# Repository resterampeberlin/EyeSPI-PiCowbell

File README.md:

# Purpose

# Credits

This open source code project is has been proudfully produced in Berlin (and other places around the globe) by

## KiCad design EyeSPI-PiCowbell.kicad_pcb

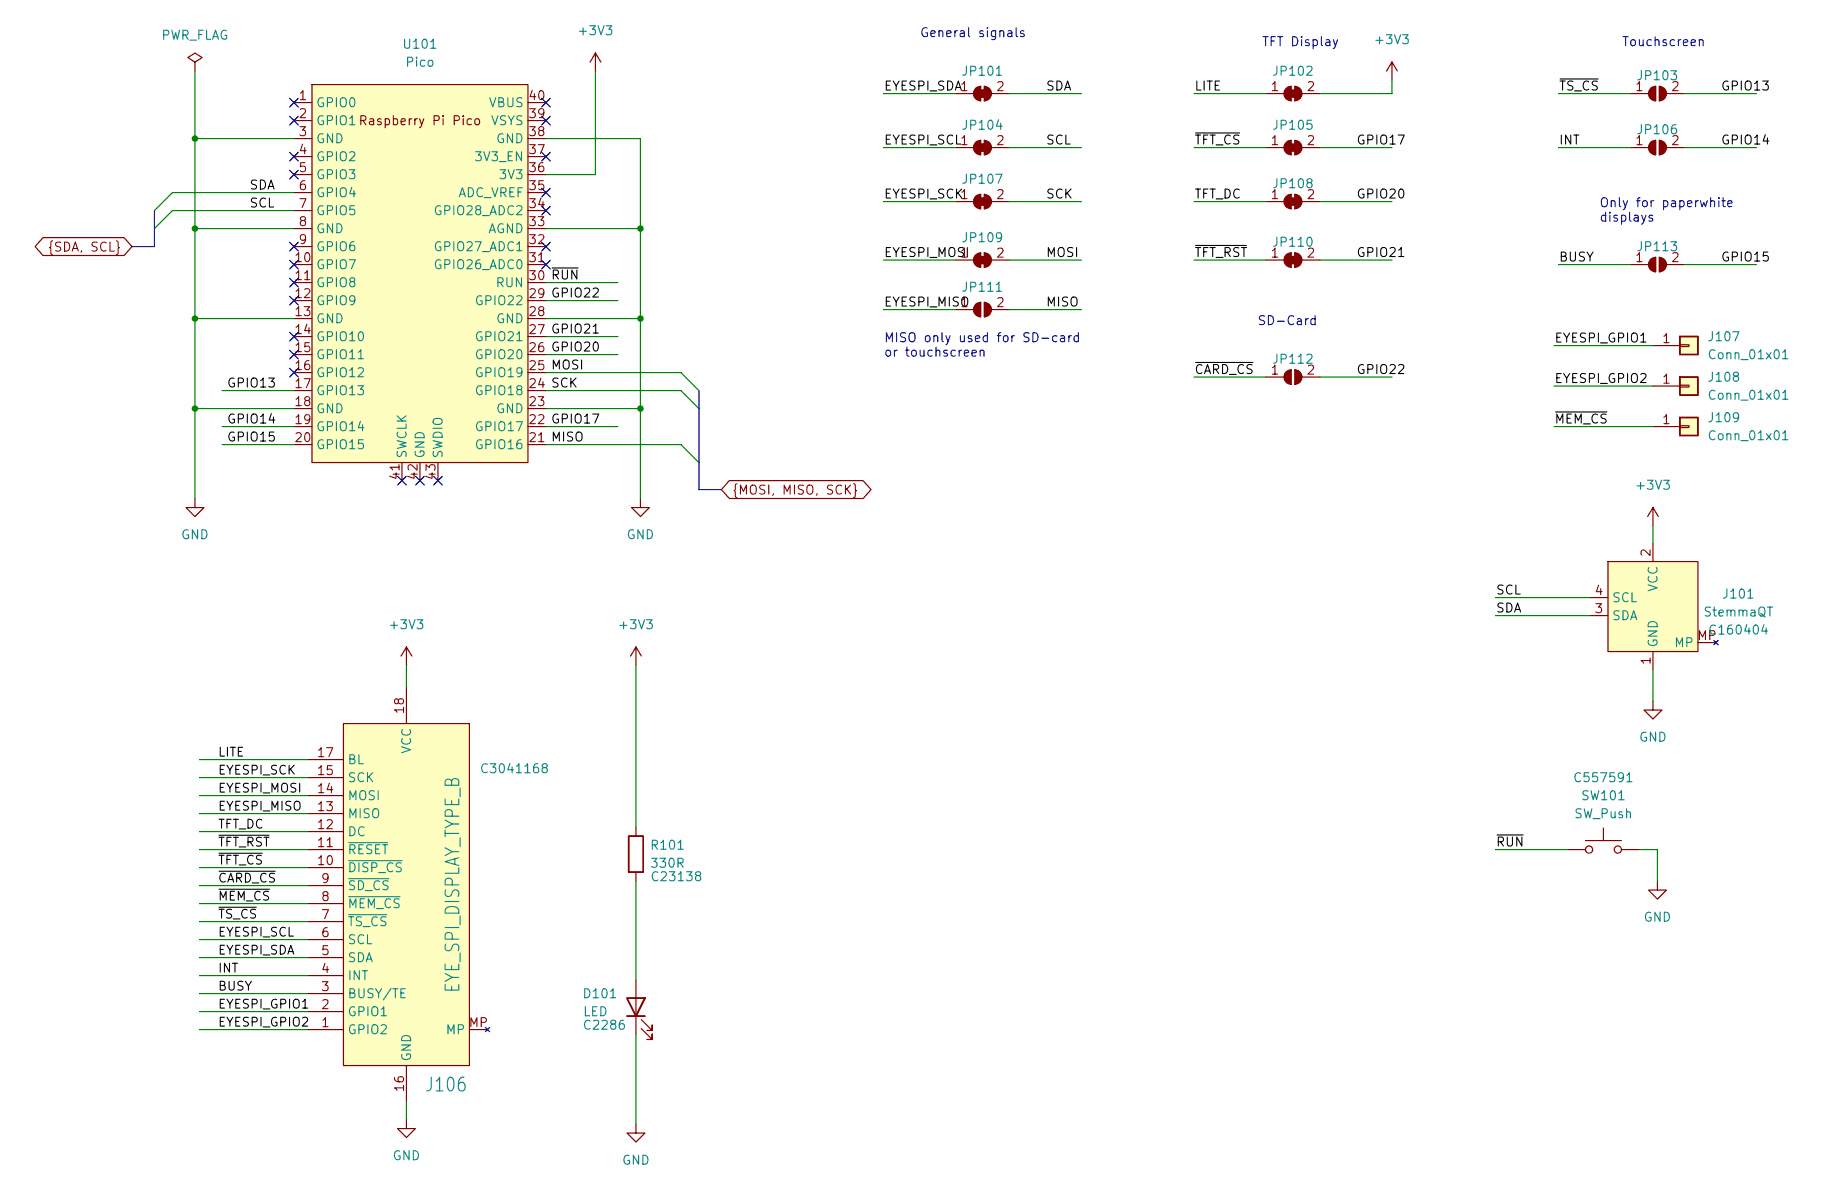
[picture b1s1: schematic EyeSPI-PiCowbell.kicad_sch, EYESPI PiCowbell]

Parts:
D101: LED; LED_0603_1608Metric_Pad1.05x0.95mm_HandSolder; LCSC C2286
J101: StemmaQT; JST_SH_SM04B-SRSS-TB_1x04-1MP_P1.00mm_Horizontal; LCSC C160404
J106: EYE_SPI_DISPLAY_TYPE_B; Hirose_FH12-18S-0.5SH_1x18-1MP_P0.50mm_Horizontal; LCSC C3041168
J107, J108, J109: Conn_01x01; SolderWire-0.25sqmm_1x01_D0.65mm_OD1.7mm
JP101, JP102, JP104, JP105, JP107, JP108, JP109, JP110: SolderJumper_2_Bridged; SolderJumper-2_P1.3mm_Bridged_Pad1.0x1.5mm
JP103, JP106, JP111, JP112, JP113: SolderJumper_2_Open; SolderJumper-2_P1.3mm_Open_Pad1.0x1.5mm
R101: 330R; R_0603_1608Metric_Pad0.98x0.95mm_HandSolder; LCSC C23138
SW101: SW_Push; Switch_SMD_3.95x2.9mm; LCSC C557591
U101: Pico; RPi_Pico_SMD_TH

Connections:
+3V3: J101.2 (VCC), J106.18 (VCC), JP102.2 (B), R101.1, U101.36 (3V3)
/BUSY: J106.3 (BUSY/TE), JP113.1 (A)
/EYESPI_GPIO1: J106.2 (GPIO1), J107.1
/EYESPI_GPIO2: J106.1 (GPIO2), J108.1
/EYESPI_MISO: J106.13 (MISO), JP111.1 (A)
/EYESPI_MOSI: J106.14 (MOSI), JP109.1 (A)
/EYESPI_SCK: J106.15 (SCK), JP107.1 (A)
/EYESPI_SCL: J106.6 (SCL), JP104.1 (A)
/EYESPI_SDA: J106.5 (SDA), JP101.1 (A)
/GPIO13: JP103.2 (B), U101.17 (GPIO13)
/GPIO14: JP106.2 (B), U101.19 (GPIO14)
/GPIO15: JP113.2 (B), U101.20 (GPIO15)
/GPIO17: JP105.2 (B), U101.22 (GPIO17)
/GPIO20: JP108.2 (B), U101.26 (GPIO20)
/GPIO21: JP110.2 (B), U101.27 (GPIO21)
/GPIO22: JP112.2 (B), U101.29 (GPIO22)
/INT: J106.4 (INT), JP106.1 (A)
/LITE: J106.17 (BL), JP102.1 (A)
/TFT_DC: J106.12 (DC), JP108.1 (A)
/~CARD_CS: J106.9 (~SD_CS), JP112.1 (A)
/~MEM_CS: J106.8 (~MEM_CS), J109.1
/~RUN: SW101.1, U101.30 (RUN)
/~TFT_CS: J106.10 (~DISP_CS), JP105.1 (A)
/~TFT_RST: J106.11 (~RESET), JP110.1 (A)
/~TS_CS: J106.7 (~TS_CS), JP103.1 (A)
GND: D101.1 (K), J101.1 (GND), J106.16 (GND), SW101.2, U101.3 (GND), U101.8 (GND), U101.13 (GND), U101.18 (GND), U101.23 (GND), U101.28 (GND), U101.33 (AGND), U101.38 (GND)
MISO: JP111.2 (B), U101.21 (GPIO16)
MOSI: JP109.2 (B), U101.25 (GPIO19)
unnamed: D101.2 (A), R101.2
SCK: JP107.2 (B), U101.24 (GPIO18)
SCL: J101.4 (SCL), JP104.2 (B), U101.7 (GPIO5)
SDA: J101.3 (SDA), JP101.2 (B), U101.6 (GPIO4)

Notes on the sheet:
General signals
MISO only used for SD-card or touchscreen
Touchscreen
TFT Display
Only for paperwhite displays
SD-Card

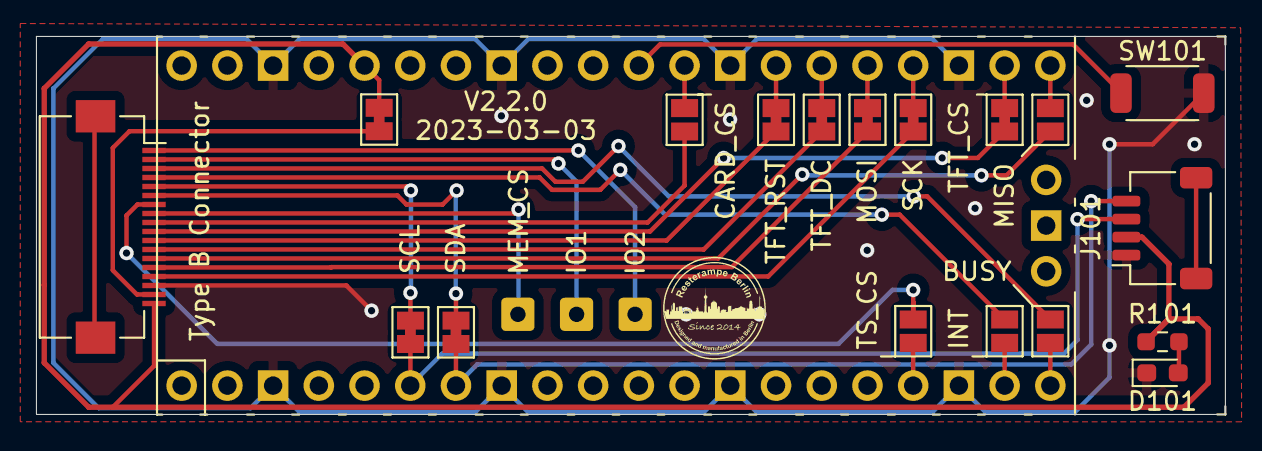
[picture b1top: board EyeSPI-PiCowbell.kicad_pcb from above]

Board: 2 copper layers, 66.1 x 21.0 mm, 22 parts (1 on the bottom side), 32 nets.

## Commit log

2023-01-17 Initial version
2023-01-21 Production
2023-01-21 Documentation updated
2023-02-09 Closed #1 #2 #3
2023-02-09 Closes #1 #2 #3
2023-03-02 Closed #4 update to KiCad 7
2023-03-03 Placed FPC connector outside Pico

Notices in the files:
EyeSPI-PiCowbell.kicad_pcb:
https://creativecommons.org/licenses/by-nc/4.0
License CC BY-NC 4.0
